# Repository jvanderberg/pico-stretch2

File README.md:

# Pico Stretch 2

An RP2350B dev board that breaks out all 48 GPIO pins while following the original Raspberry Pi Pico footprint for the first 20 pins on each side. It adds another 12 pins on each side — keeping the same 0.1" pitch and castellated edges so it remains breadboard-friendly.

The board supports PSRam (chip select on GP0 or GP47) and the Radio Module 2 for WiFi/BT

Features:
- USB-C connector
- Boot/Reset buttons
- SWDIO debugging header
- Radio Module 2 footprint / jumpers
- PSRam footprint / jumper
- Breaks out all 48 GPIOs
- Supports existing Pi Pico pinout projects (if there's room for a little overhang, or if you want to get adventuresome and saw the board in half)

## Board views

**Top**

**Bottom**

## PCB layout

**F.Cu / F.Silkscreen**

**B.Cu / B.Silkscreen (mirrored)**

## Pinout

```
1   GPIO0           64  VBUS
2   GPIO1           63  VSYS
3   GND             62  GND
4   GPIO2           61  3v3_EN
5   GPIO3           60  3v3
6   GPIO4           59  ADC_VREF
7   GPIO5           58  GPIO28
8   GND             57  GND
9   GPIO6           56  GPIO27
10  GPIO7           55  GPIO26
11  GPIO8           54  RUN
12  GPIO9           53  GPIO22
13  GND             52  GND
14  GPIO10          51  GPIO21
15  GPIO11          50  GPIO20
16  GPIO12          49  GPIO19
17  GPIO13          48  GPIO18
18  GND             47  GND
19  GPIO14          46  GPIO17
20  GPIO15          45  GPIO16
21  GPIO23          44  GPIO47/ADC7
22  GPIO24          43  GPIO46/ADC6
23  GPIO25          42  GPIO45/ADC5
24  GPIO29          41  GPIO44/ADC4
25  GPIO30          40  GPIO43/ADC3
26  GPIO31          39  GPIO42/ADC2
27  GPIO32          38  GPIO41/ADC1
28  GPIO33          37  GPIO40/ADC0
29  GPIO34          36  GPIO39
30  GPIO35          35  GPIO38
31  GND             34  GND
32  GPIO36          33  GPIO37
```

## Optional parts and pin notes

- **PSRAM (U6)** is not fitted by default. Solder an APS6404L-3SQR (3.3 V, SOP-8) and close **one** of the
  chip-select jumpers on the back: JP1 puts it on GPIO0, JP4 on GPIO47 (the RP2350 can use either as its
  second QSPI chip select, QMI CS1n). Never close both. GPIO47 keeps GPIO0 free for UART0 TX and matches other
  RP2350B PSRAM boards; the jumper you close takes that pin away from the castellated pad.
- **Radio (U5, Raspberry Pi RM2)** is not fitted by default. GPIO24 (data/IRQ) and GPIO29 (clock) are wired
  straight to its pads; GPIO25 (CS) and GPIO23 (WL_ON) go through JP2 and JP3. With the radio fitted and
  the jumpers closed, all four belong to the radio.
- The RM2 antenna hangs past the end of the board. If you solder this board onto a carrier that extends
  under that end, keep copper off the carrier under and around the antenna.
- Wi-Fi transmit is bursty. The 3.3 V supply is a linear regulator, so avoid sustained full-rate transmit
  and keep extra load on the 3V3 pin modest. Keep VSYS above about 3.5 V.
- The flash and PSRAM share a QSPI bus with three loads and no series resistors. The Pico 2 runs its flash
  at `PICO_FLASH_SPI_CLKDIV 2`. If you see flash or PSRAM errors at higher system clocks, use a larger
  divider (4) and test before going back down.

## Back side

- Every castellated pad is labelled on the back too, with the same text as the front.
- Jumpers: JP1 = PSRAM CS on GPIO0, JP4 = PSRAM CS on GPIO47, JP2 + JP3 = radio (see above).
- Test pads: TP1 = 1V1, TP2 = 3V3, TP3 = USB D-, TP4 = USB D+ (on the connector side of the 33 Ω
  resistors, labelled D- and D+), TP5 = GND (labelled G).
- TP3, TP4 and TP5 sit exactly where the Pico / Pico 2 has its USB test points (its TP2 = D-, TP3 = D+,
  TP1 = GND), with the same 1.5 x 1.5 mm pads, so a carrier made for the Pico SMT footprint reaches USB
  through them.

## Soldering onto a Pico footprint

The first 20 castellated pads on each side, and the USB test pads above, line up with the Raspberry Pi Pico /
Pico 2 SMT footprint (Pico 2 datasheet section 3.2), so the board can be hot-plate or reflow soldered onto a
carrier designed for a Pico. The other 24 pads and the radio end overhang the Pico outline.

- Nothing else on the back lands on that footprint's pads: its TP4-TP7 positions are bare board here, and its
  four USB shell pads (A-D) meet only this board's USB-C shell legs (GND, as on the Pico) and its plastic
  locating pegs, which stay inside the board.
- Leave the SWD header (J2) unfitted, or cut it flush: its pins would stop the board sitting flat.

## Production files for JLCPCB

Production files live in the `production/` directory, written by
[JLCImport](https://github.com/jvanderberg/kicad_jlcimport)'s `jlcimport-cli production` from the board as it is:

- `pico-stretch2-gerbers.zip` — Gerber and drill files (the same files, unzipped, are in `gerbers/`)
- `pico-stretch2-bom.csv` — bill of materials
- `pico-stretch2-cpl.csv` — component placement file, with rotations solved against JLC's own footprints
- `pico-stretch2-report.txt` — the production check: stock, part types, fees, and the placements to look at in
  JLC's preview

To regenerate after a board change: `jlcimport-cli production pico-stretch2.kicad_pcb` (add `--force` to write
the files even when the check reports an error, such as a part out of stock).

When ordering:

- Choose epoxy-filled and capped vias: the board has vias in pads.
- Select the castellated holes option.
- Use the JLC04161H-7628 stackup (set in the board file).
- U5 (RM2) and U6 (PSRAM) are marked DNP and left out of the BOM and placement files; clear DNP if you want JLC
  to fit U6.
- L1 (AOTA-B201610S3R3-101-T, C42411119) is often out of stock at JLC: pre-order it into your JLC parts
  library or consign it. Do not substitute another inductor; the RP2350 regulator needs this
  polarity-marked part.
- Check pin 1 of U1, U3, U4 and the diodes, and the LED, in JLC's placement preview.

## Regenerating images

Run [`scripts/render-images.sh`](scripts/render-images.sh) after PCB changes to regenerate everything in `images/`. Requires `kicad-cli` (KiCad ≥ 9) and ImageMagick (`magick`).

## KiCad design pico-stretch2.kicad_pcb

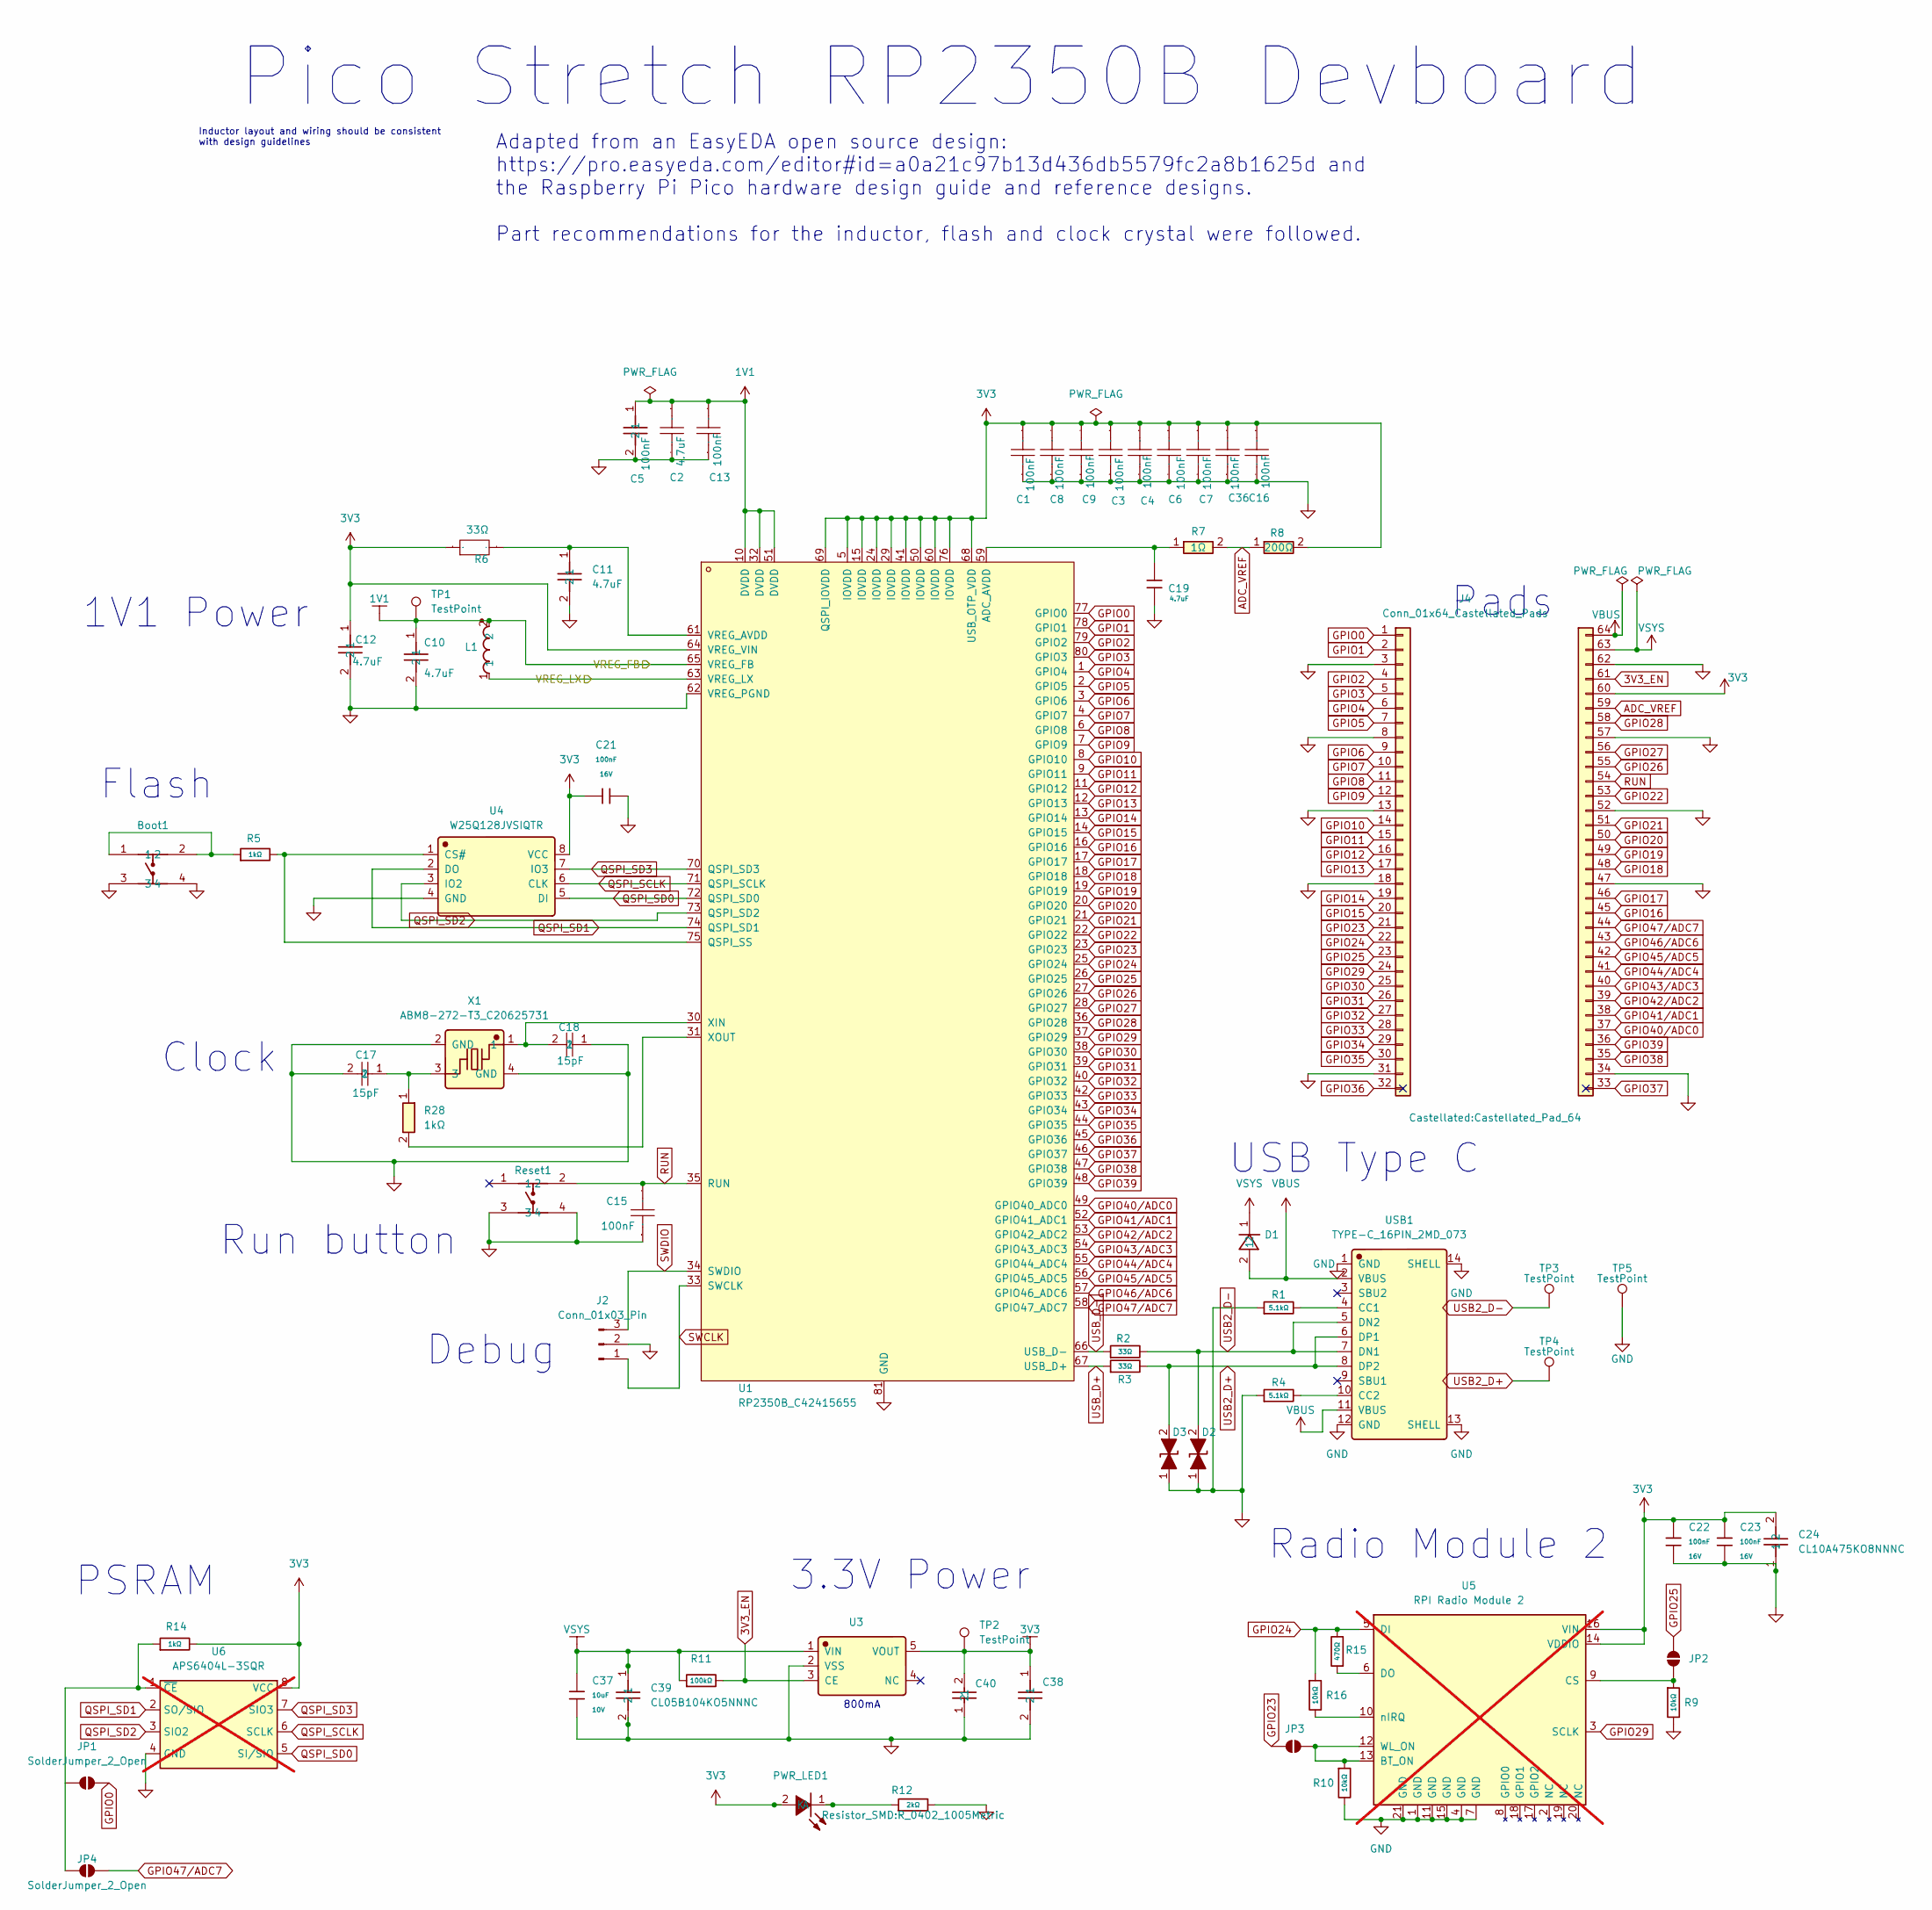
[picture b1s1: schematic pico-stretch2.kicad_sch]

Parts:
Boot1: K2-1808SN-A4SW; Manufacturer Part K2-1808SN-A4SW-01; LCSC C92589
C1, C3, C4, C6, C7, C8, C9, C13, C15, C16, C36: 100nF; C_0402_1005Metric; Manufacturer Part CL05B104KO5NNNC; LCSC Part Name 100nF ±10% 16V
C2, C10, C11, C12: 4.7uF; C_0402_1005Metric; Manufacturer Part CL05A475MP5NRNC; LCSC C23733
C5: 100nF; C_0402_1005Metric; Manufacturer Part CL05B104KO5NNNC; LCSC C1525
C17, C18: 15pF; C_0402_1005Metric; Manufacturer Part 0402CG150J500NT; LCSC Part Name 15pF ±5% 50V
C19: 4.7uF; C_0402_1005Metric; Voltage Rated 10V; Tolerance ±20%; Part CL05A475MP5NRNC; LCSC C23733
C21, C22, C23: 100nF; C_0402_1005Metric; Voltage Rated 16V; Tolerance ±10%; Part CL05B104KO5NNNC; LCSC C1525
C24: CL10A475KO8NNNC; C_0603_1608Metric; Manufacturer Part CL10A475KO8NNNC; LCSC C19666
C37, C40: 10uF; C_0603_1608Metric; Voltage Rated 10V; Tolerance ±10%; Part CL10A106KP8NNNC; LCSC C19702
C38, C39: CL05B104KO5NNNC; C_0402_1005Metric; Manufacturer Part CL05B104KO5NNNC; LCSC C1525
D1: DFLS130L-7; D_PowerDI-123; Manufacturer Part DFLS130L-7; LCSC C110493
D2, D3: RCLAMP0521P_TCT_C3029033; Manufacturer Part RCLAMP0521P.TCT-MS; LCSC C3029033
J2: Conn_01x03_Pin; PinHeader_1x03_P2.54mm_Vertical
J4: Conn_01x64_Castellated_Pads; Castellated_Pad_64
JP1, JP2, JP3, JP4: SolderJumper_2_Open; SolderJumper-2_P1.3mm_Open_Pad1.0x1.5mm
L1: AOTA-B201610S3R3-101-T; Manufacturer Part AOTA-B201610S3R3-101-T; LCSC C42411119
PWR_LED1: KT-0603R; Manufacturer Part KT-0603R; LCSC C2286
R1, R4: 5.1kΩ; R_0402_1005Metric; Overload Voltage (Max) 50V; Tolerance ±1%; Part 0402WGF5101TCE; LCSC C25905
R2, R3: 33Ω; R_0402_1005Metric; Overload Voltage (Max) 50V; Tolerance ±1%; Part 0402WGF330JTCE; LCSC C25105
R5, R14: 1kΩ; R_0402_1005Metric; Overload Voltage (Max) 50V; Tolerance ±1%; Part 0402WGF1001TCE; LCSC C11702
R6: 33Ω; R_0402_1005Metric; Manufacturer Part 0402WGF330JTCE; LCSC Part Name 33Ω ±1% 62.5mW 厚膜电阻
R7: 1Ω; R_0402_1005Metric; Manufacturer Part 0402WGF100KTCE; LCSC C25086
R8: 200Ω; R_0402_1005Metric; Manufacturer Part 0402WGF2000TCE; LCSC C25087
R9, R10, R16: 10kΩ; R_0402_1005Metric; Overload Voltage (Max) 50V; Tolerance ±1%; Part 0402WGF1002TCE; LCSC C25744
R11: 100kΩ; R_0402_1005Metric; Overload Voltage (Max) 50V; Tolerance ±1%; Part 0402WGF1003TCE; LCSC C25741
R12: 2kΩ; R_0402_1005Metric; Overload Voltage (Max) 50V; Tolerance ±1%; Part 0402WGF2001TCE; LCSC C4109
R15: 470Ω; R_0402_1005Metric; Overload Voltage (Max) 50V; Tolerance ±1%; Part 0402WGF4700TCE; LCSC C25117
R28: 1kΩ; R_0402_1005Metric; Manufacturer Part 0402WGF1001TCE; LCSC C11702
Reset1: K2-1808SN-A4SW; Manufacturer Part K2-1808SN-A4SW-01; LCSC C92589
TP1, TP2: TestPoint; TestPoint_Pad_1.0x1.0mm
TP3, TP4, TP5: TestPoint; TestPoint_Pad_1.5x1.5mm_R0.3mm
U1: RP2350B_C42415655; Manufacturer Part RP2350B; LCSC C42415655
U3: ME6217C33M5G; SOT-23-5; Manufacturer Part ME6217C33M5G; LCSC C427602
U4: W25Q128JVSIQTR; SOIC-8_5.3x5.3mm_P1.27mm; Manufacturer Part W25Q128JVSIQ; LCSC C97521
U5: RPI Radio Module 2; rpi_rmc20452t; not fitted
U6: APS6404L-3SQR; SOIC-8_3.9x4.9mm_P1.27mm; LCSC C5333729; not fitted
USB1: TYPE-C_16PIN_2MD_073; Manufacturer Part TYPE-C 16PIN 2MD(073); LCSC C2765186
X1: ABM8-272-T3_C20625731; Manufacturer Part ABM8-272-T3; LCSC C20625731

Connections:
1V1: C2.1, C5.1, C10.1, C13.2, L1.2, TP1.1 (1_1), U1.10 (DVDD), U1.32 (DVDD), U1.51 (DVDD), U1.65 (VREG_FB)
3V3: C1.1, C3.1, C4.1, C6.1, C7.1, C8.2, C9.2, C12.1, C16.1, C21.1, C22.1, C23.1, C24.2, C36.2, C38.1, C40.2, J4.60, PWR_LED1.2 (A), R6.1, R8.2, R14.2, TP2.1 (1_1), U1.5 (IOVDD), U1.15 (IOVDD), U1.24 (IOVDD), U1.29 (IOVDD), U1.41 (IOVDD), U1.50 (IOVDD), U1.60 (IOVDD), U1.64 (VREG_VIN), U1.68 (USB_OTP_VDD), U1.69 (QSPI_IOVDD), U1.76 (IOVDD), U3.5 (VOUT), U4.8 (VCC), U5.14 (VDDIO), U5.16 (VIN), U6.8 (VCC)
3V3_EN: J4.61, R11.2, U3.3 (CE)
/VREG_LX: L1.1, U1.63 (VREG_LX)
ADC_VREF: J4.59, R7.2, R8.1
GND: Boot1.3, Boot1.4, C1.2, C2.2, C3.2, C4.2, C5.2, C6.2, C7.2, C8.1, C9.1, C10.2, C11.2, C12.2, C13.1, C15.1, C16.2, C17.2, C18.1, C19.2, C21.2, C22.2, C23.2, C24.1, C36.1, C37.2, C38.2, C39.2, C40.1, D2.1, D3.1, J2.2, J4.3, J4.8, J4.13, J4.18, J4.31, J4.34, J4.47, J4.52, J4.57, J4.62, R1.1, R4.1, R9.2, R10.2, R12.2, Reset1.3, Reset1.4, TP5.1, U1.62 (VREG_PGND), U1.81 (GND), U3.2 (VSS), U4.4 (GND), U5.1 (GND), U5.4 (GND), U5.7 (GND), U5.11 (GND), U5.15 (GND), U5.21 (GND), U6.4 (GND), USB1.1 (GND), USB1.12 (GND), USB1.13 (SHELL), USB1.14 (SHELL), X1.2 (GND), X1.4 (GND)
GPIO0: J4.1, JP1.2 (B), U1.77 (GPIO0)
GPIO1: J4.2, U1.78 (GPIO1)
GPIO2: J4.4, U1.79 (GPIO2)
GPIO3: J4.5, U1.80 (GPIO3)
GPIO4: J4.6, U1.1 (GPIO4)
GPIO5: J4.7, U1.2 (GPIO5)
GPIO6: J4.9, U1.3 (GPIO6)
GPIO7: J4.10, U1.4 (GPIO7)
GPIO8: J4.11, U1.6 (GPIO8)
GPIO9: J4.12, U1.7 (GPIO9)
GPIO10: J4.14, U1.8 (GPIO10)
GPIO11: J4.15, U1.9 (GPIO11)
GPIO12: J4.16, U1.11 (GPIO12)
GPIO13: J4.17, U1.12 (GPIO13)
GPIO14: J4.19, U1.13 (GPIO14)
GPIO15: J4.20, U1.14 (GPIO15)
GPIO16: J4.45, U1.16 (GPIO16)
GPIO17: J4.46, U1.17 (GPIO17)
GPIO18: J4.48, U1.18 (GPIO18)
GPIO19: J4.49, U1.19 (GPIO19)
GPIO20: J4.50, U1.20 (GPIO20)
GPIO21: J4.51 (Pin_61), U1.21 (GPIO21)
GPIO22: J4.53, U1.22 (GPIO22)
GPIO23: J4.21, JP3.1 (A), U1.23 (GPIO23)
GPIO24: J4.22, R15.2, R16.1, U1.25 (GPIO24), U5.5 (DI)
GPIO25: J4.23, JP2.2 (B), U1.26 (GPIO25)
GPIO26: J4.55, U1.27 (GPIO26)
GPIO27: J4.56, U1.28 (GPIO27)
GPIO28: J4.58, U1.36 (GPIO28)
GPIO29: J4.24, U1.37 (GPIO29), U5.3 (SCLK)
GPIO30: J4.25, U1.38 (GPIO30)
GPIO31: J4.26, U1.39 (GPIO31)
GPIO32: J4.27, U1.40 (GPIO32)
GPIO33: J4.28, U1.42 (GPIO33)
GPIO34: J4.29, U1.43 (GPIO34)
GPIO35: J4.30, U1.44 (GPIO35)
GPIO36: J4.32, U1.45 (GPIO36)
GPIO37: J4.33, U1.46 (GPIO37)
GPIO38: J4.35, U1.47 (GPIO38)
GPIO39: J4.36, U1.48 (GPIO39)
GPIO40/ADC0: J4.37, U1.49 (GPIO40_ADC0)
GPIO41/ADC1: J4.38, U1.52 (GPIO41_ADC1)
GPIO42/ADC2: J4.39, U1.53 (GPIO42_ADC2)
GPIO43/ADC3: J4.40, U1.54 (GPIO43_ADC3)
GPIO44/ADC4: J4.41, U1.55 (GPIO44_ADC4)
GPIO45/ADC5: J4.42, U1.56 (GPIO45_ADC5)
GPIO46/ADC6: J4.43, U1.57 (GPIO46_ADC6)
GPIO47/ADC7: J4.44, JP4.2 (B), U1.58 (GPIO47_ADC7)
unnamed: Boot1.1, Boot1.2, R5.1
unnamed: C17.1, R28.1, X1.3
unnamed: JP1.1 (A), JP4.1 (A), R14.1, U6.1 (~CE)
unnamed: JP2.1 (A), R9.1, U5.9 (CS)
unnamed: JP3.2 (B), R10.1, U5.12 (WL_ON), U5.13 (BT_ON)
unnamed: PWR_LED1.1 (K), R12.1
unnamed: C19.1, R7.1, U1.59 (ADC_AVDD)
unnamed: R5.2, U1.75 (QSPI_SS), U4.1 (CS#)
unnamed: C11.1, R6.2, U1.61 (VREG_AVDD)
unnamed: C18.2, U1.30 (XIN), X1.1
unnamed: R28.2, U1.31 (XOUT)
unnamed: R15.1, U5.6 (DO)
unnamed: R16.2, U5.10 (nIRQ)
unnamed: R1.2, USB1.4 (CC1)
unnamed: R4.2, USB1.10 (CC2)
QSPI_SCLK: U1.71 (QSPI_SCLK), U4.6 (CLK), U6.6 (SCLK)
QSPI_SD0: U1.72 (QSPI_SD0), U4.5 (DI), U6.5 (SI/SIO)
QSPI_SD1: U1.74 (QSPI_SD1), U4.2 (DO), U6.2 (SO/SIO)
QSPI_SD2: U1.73 (QSPI_SD2), U4.3 (IO2), U6.3 (SIO2)
QSPI_SD3: U1.70 (QSPI_SD3), U4.7 (IO3), U6.7 (SIO3)
RUN: C15.2, J4.54, Reset1.2, U1.35 (RUN)
SWCLK: J2.1, U1.33 (SWCLK)
SWDIO: J2.3, U1.34 (SWDIO)
USB2_D+: D3.2, R3.2, TP4.1, USB1.6 (DP1), USB1.8 (DP2)
USB2_D-: D2.2, R2.2, TP3.1, USB1.5 (DN2), USB1.7 (DN1)
USB_D+: R3.1, U1.67 (USB_D+)
USB_D-: R2.1, U1.66 (USB_D-)
VBUS: D1.2, J4.64, USB1.2 (VBUS), USB1.11 (VBUS)
VSYS: C37.1, C39.1, D1.1, J4.63, R11.1, U3.1 (VIN)

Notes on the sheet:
Clock
PSRAM
USB Type C
Flash
3.3V Power
Radio Module 2
Debug
Run button
Pico Stretch RP2350B Devboard
Inductor layout and wiring should be consistent with design guidelines
1V1 Power
Pads
Adapted from an EasyEDA open source design: https://pro.easyeda.com/editor#id=a0a21c97b13d436db5579fc2a8b1625d and the Raspberry Pi Pico hardware design guide and reference designs. Part recommendations for the inductor, flash and clock crystal were followed.
800mA

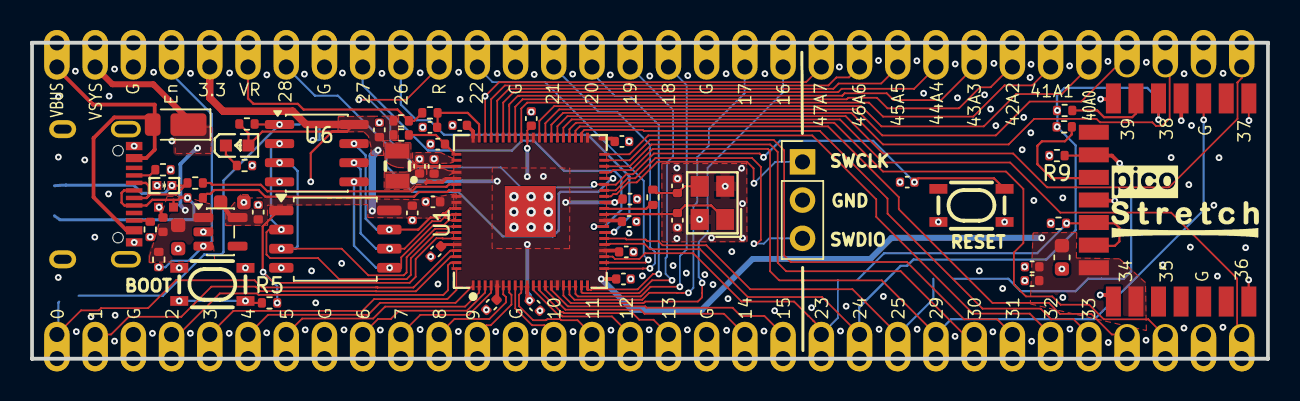
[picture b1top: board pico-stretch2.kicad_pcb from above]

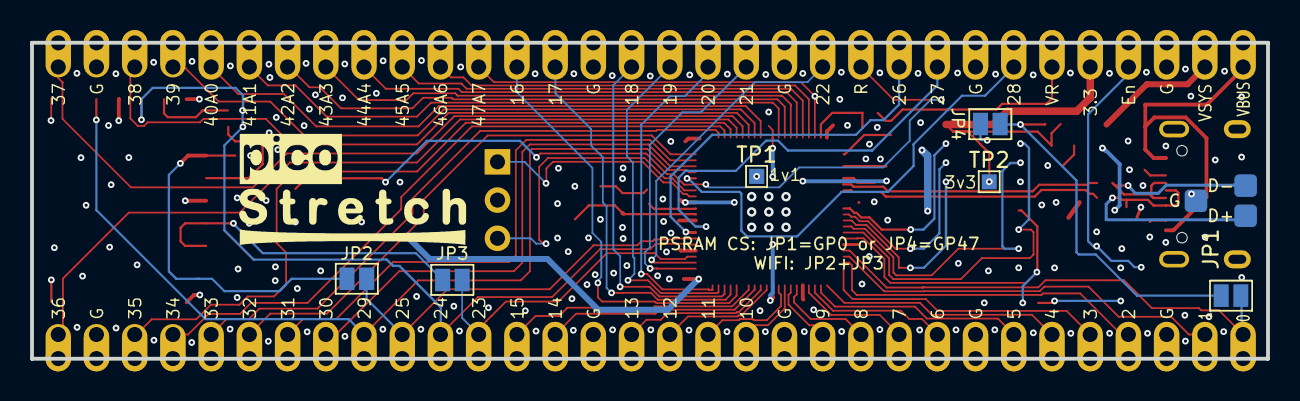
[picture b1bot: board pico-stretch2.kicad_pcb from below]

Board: 4 copper layers, 82.1 x 21.0 mm, 68 parts (9 on the bottom side), 83 nets.

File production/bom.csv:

Designator,Footprint,Quantity,Value,LCSC Part #
"BOOT1, RESET1",K2-1808SN-A4SW,2,K2-1808SN-A4SW,C92589
"C1, C13, C16, C2, C21, C22, C23, C3, C36, C4, C6, C7, C8",0402,13,100nF,C1525
"C10, C11, C12, C19, C5",0402,5,4.7uF,C23733
"C15, C9",0402,2,100nF,C14663
"C17, C18",0402,2,15pF,C1548
C24,0603,1,CL10A475KO8NNNC,C19666
C37,0603,1,10uF,C19702
"C38, C39",0402,2,CL05B104KO5NNNC,C1525
C40,0402,1,CL05A106MQ5NUNC,C15525
D1,D_PowerDI-123,1,DFLS130L-7,C110493
"D2, D3",RCLAMP0521P_TCT_C3029033,2,RCLAMP0521P_TCT_C3029033,C3029033
J2,PinHeader_1x03_P2.54mm_Vertical,1,Conn_01x03_Pin,
J4,Castellated_Pad_64,1,Conn_01x64_Castellated_Pads,
L1,AOTA-B201610S3R3-101-T,1,AOTA-B201610S3R3-101-T,C42411119
PWR_LED1,KT-0603R,1,KT-0603R,C2286
"R1, R4",0402,2,5.1kΩ,C25905
"R10, R14, R16, R9",0402,4,10kΩ,C25744
R11,0402,1,100kΩ,C25741
R12,0402,1,2kΩ,C4109
R15,0402,1,470Ω,C25117
"R2, R3, R6",0402,3,33Ω,C25105
"R28, R5",0402,2,1kΩ,C11702
R7,0402,1,1Ω,C25086
R8,0402,1,200Ω,C25087
"TP1, TP2, TP3, TP4",TestPoint_Pad_1.0x1.0mm,4,TestPoint,
U1,RP2350B_C42415655,1,RP2350B_C42415655,C42415655
U3,SOT-23-5,1,ME6217C33M5G,C427602
U4,SOIC-8_5.3x5.3mm_P1.27mm,1,W25Q128JVSIQTR,C97521
U5,rpi_rmc20452t,1,RPI Radio Module 2,
USB1,TYPE-C_16PIN_2MD_073,1,TYPE-C_16PIN_2MD_073,C2765186
X1,ABM8-272-T3_C20625731,1,ABM8-272-T3_C20625731,C20625731

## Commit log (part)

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2026-05-18 Initial commit: Pico Stretch 2 RP2350B dev board
